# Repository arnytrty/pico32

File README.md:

# Arnytrty Pico32

Pico32 is small (13mm*13mm) open source board based on ESP32-PICO-D4. It was designed for full use of the SoC package from Espressif & make it more accessible so you can simply handsolder without any special tools. It has a 4MB embedded flash ([esp32-pico-d4 datasheet](https://www.espressif.com/sites/default/files/documentation/esp32-pico-d4_datasheet_en.pdf)).

This board does not have USB to UART converter, you will need an external one to program it (they are pretty cheap). For a programming guide, check out [`FLASHING.md`](FLASHING.md).

---

## Files & Revisions:

Main folders:

| Name | Content |
|:-----|:--------|
| hardware | board CAD files |
| images | images of the board |
| models | Exported 3D models |
| order | GERBER, BOM & CPL files |

Subfolders:
| Name | Revision | Tested | Comment |
|:-----|:--------:|:------:|:--------|
| pico32_v1_jlcpcb_assembly | v1 | YES | got removeable frame to match jlcpcb assembly requirements; designed in [EasyEDA](https://easyeda.com/); fully working, but has pins from bootm & got only 100mA regulator
| pico32_v2 | v2 | NO | pins from side; better regulator; designed in [KiCad](https://www.kicad.org/)
| pico32_v2_jlcpcb_assembly | v2 | NO | got removeable frame to match jlcpcb assembly requirements, other parameters are the same as pico32_v2

***Currently I dont sell these myself, but you can check out how to buy them for yourself on [ORDER.md](ORDER.md) guide.***

# Revisions

## v2

This version is more universal than the first one, it also removes the flaws of v1. It has the same footprint as before (13mm*13mm), but instead of having pads on the bottom, it has them cascellated through holes on sides so you can easily solder it on a homemade PCB.

Known issues:
* NONE

## v1

This was used as the test of how many components ESP32-PICO-D4 needs, it works pretty well, but if you use CPU speed over 80MHz it will throw `Brownout detector was triggered`. With its 13mm*13mm footprint, you can simply fit it in ending of aluminium profile & control rgb leds with it.

Known issues:
* Wrong LDO - only 100mA
* Too small capacitors ?

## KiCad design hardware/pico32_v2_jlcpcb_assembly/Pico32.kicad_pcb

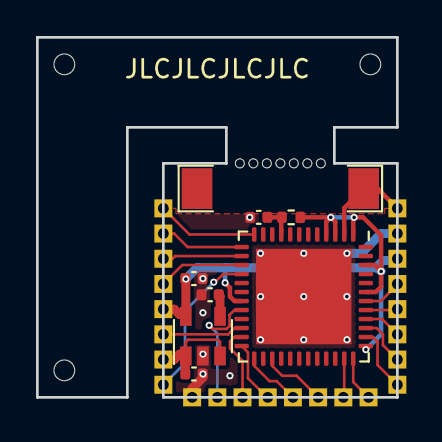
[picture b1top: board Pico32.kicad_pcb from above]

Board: 2 copper layers, 20.0 x 20.0 mm, 8 parts (0 on the bottom side), 6 nets.

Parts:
AE1: Antenna; AN9520-245
C1, C2, C4: 1uF; C_0402_1005Metric
C3: 10nF; C_0402_1005Metric
R1: 1k; R_0402_1005Metric
U1: TPS79333-EP; SOT-23-5
U2: ESP32-PICO-D4; QFN-48-1EP_7x7mm_P0.5mm_EP5.3x5.3mm

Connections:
+3V3: C2.1, R1.1, U1.5, U2.1, U2.3, U2.4, U2.19, U2.37, U2.43, U2.46
GND: C1.2, C2.2, C3.2, C4.2, U1.2, U2.49
unnamed: AE1.1, U2.2
unnamed: C3.1, U1.4
unnamed: C4.1, R1.2, U2.9
VCC: C1.1, U1.1, U1.3

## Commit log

2021-06-19 Create LICENSE
2022-02-16 Update README.md
    Fixed some vocabulary and syntax :-)
